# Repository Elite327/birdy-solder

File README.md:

# Description
My project is a bird with a button that when clicked, lights up an LED and vibrates a motor. The LED is supposed to be the eye of the bird, and the vibration is its stomach growling. There are also potentiometers to adjust the intensity of the light or vibration. This is my first PCB.

# Materials
- 1x Battery
- 1x Push Button
- 2x Potentiometers
- 1x LED
- 1x Vibration Motor

# Screenshots

# Slack Username
`Vikhyat Konchada`

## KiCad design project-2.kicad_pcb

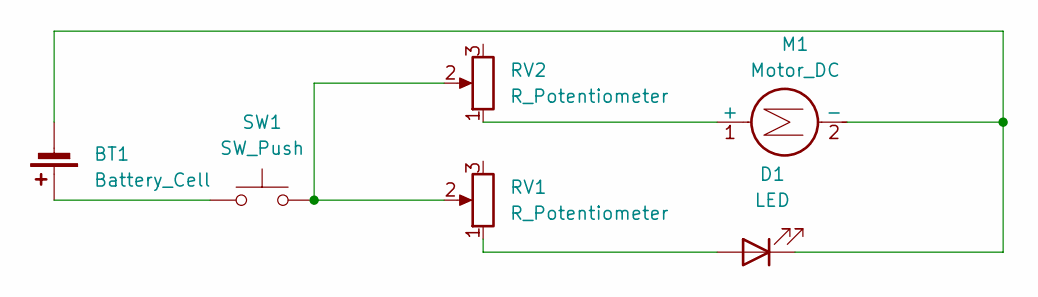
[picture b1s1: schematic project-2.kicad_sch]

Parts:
BT1: Battery_Cell; BatteryHolder_Keystone_3034_1x20mm
D1: LED; LED_D5.0mm
M1: Motor_DC; PinHeader_1x02_P2.54mm_Vertical
RV1, RV2: R_Potentiometer; Potentiometer_Vishay_T73YP_Vertical
SW1: SW_Push; SW_PUSH_6mm

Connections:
unnamed: BT1.1 (+), SW1.1
unnamed: BT1.2 (-), D1.1 (K), M1.2 (-)
unnamed: D1.2 (A), RV1.1
unnamed: M1.1 (+), RV2.1
unnamed: RV1.2, RV2.2, SW1.2

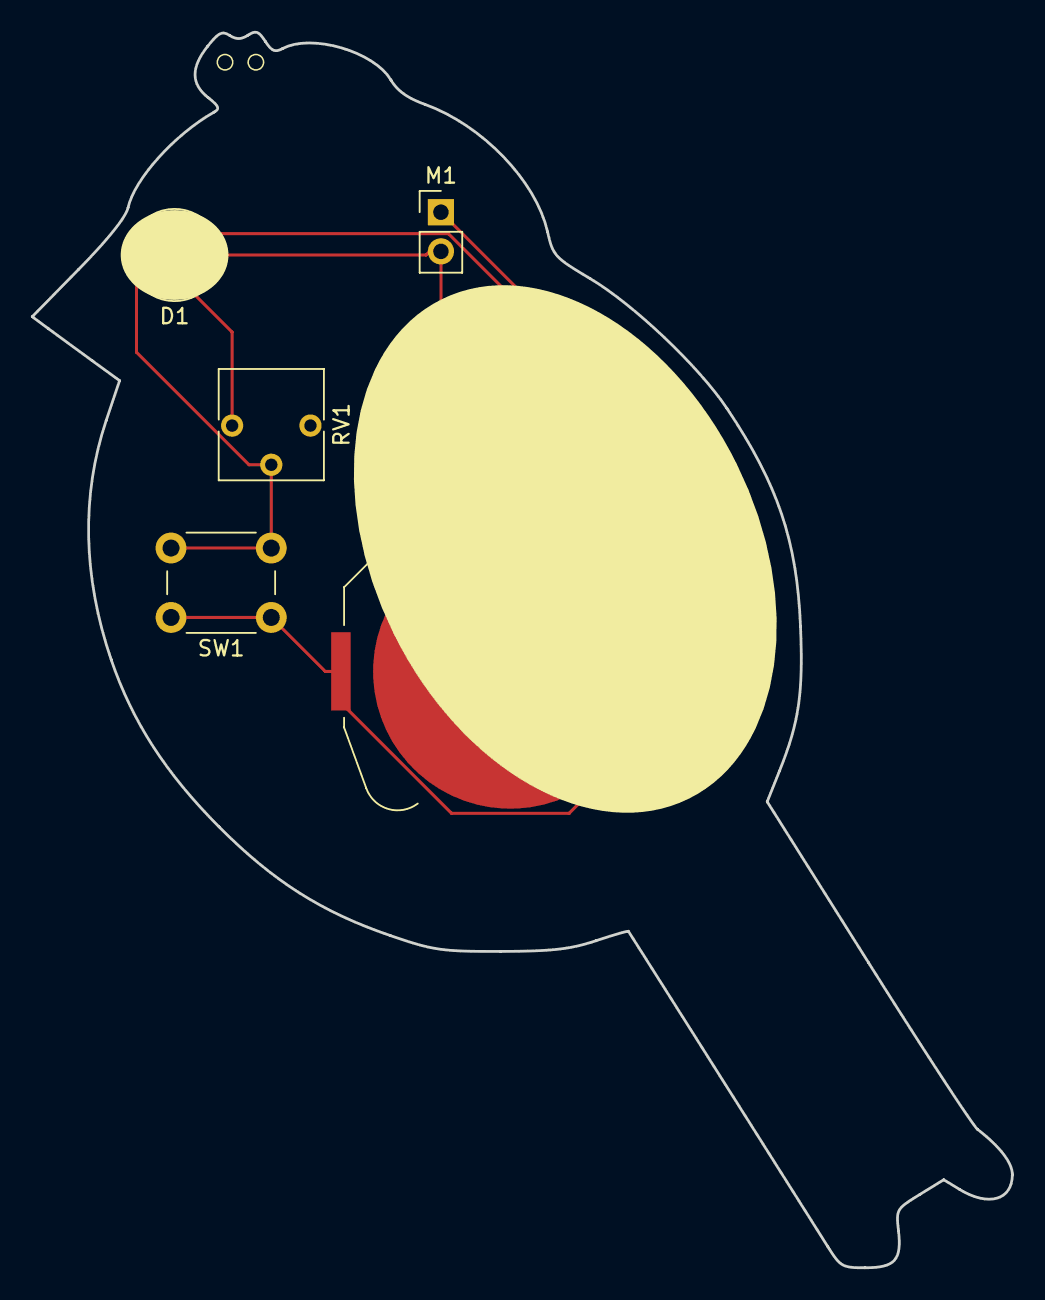
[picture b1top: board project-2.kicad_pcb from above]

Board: 2 copper layers, 63.5 x 80.1 mm, 6 parts (0 on the bottom side), 5 nets.

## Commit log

2025-05-04 added gerber and drill
2025-05-04 add pics
2025-05-04 fix circuit
2025-05-04 fix circuit 2
2025-05-04 add wwf logo
